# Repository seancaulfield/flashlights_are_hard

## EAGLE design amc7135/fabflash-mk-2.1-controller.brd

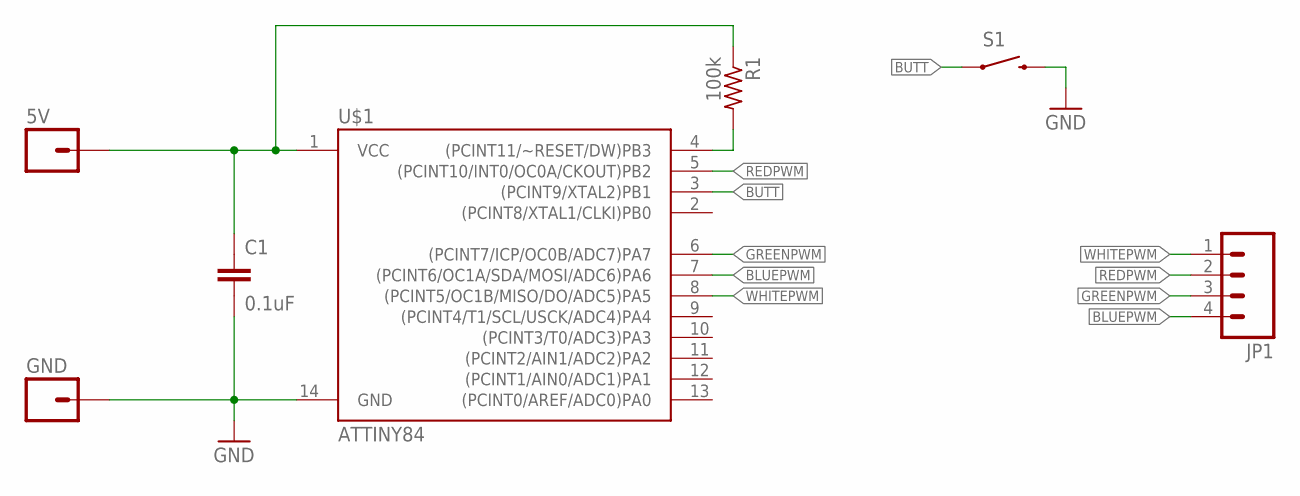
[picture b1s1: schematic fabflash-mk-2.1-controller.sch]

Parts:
5V: M01PTH-0.9MM; 1X01-0.9MM
C1: 0.1uF; C0603
GND: M01PTH-0.9MM; 1X01-0.9MM
JP1: M04JST-PTH-VERT; JST-4-PH-VERT-PTH
R1: 100k; R0603
S1: SWITCH-MOMENTARY-212MM; TACTILE-PTH-12MM
U$1: ATTINY84; SO14

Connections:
5V: 5V.1, C1.1, R1.1, U$1.1 (VCC)
BLUEPWM: JP1.4, U$1.7 ((PCINT6/OC1A/SDA/MOSI/ADC6)PA6)
BUTT: S1.1, U$1.3 ((PCINT9/XTAL2)PB1)
GND: C1.2, GND.1, S1.3 (2), U$1.14 (GND)
GREENPWM: JP1.3, U$1.6 ((PCINT7/ICP/OC0B/ADC7)PA7)
unnamed: R1.2, U$1.4 ((PCINT11/~RESET/DW)PB3)
REDPWM: JP1.2, U$1.5 ((PCINT10/INT0/OC0A/CKOUT)PB2)
WHITEPWM: JP1.1, U$1.8 ((PCINT5/OC1B/MISO/DO/ADC5)PA5)

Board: 2 copper layers, 7 parts (1 on the bottom side), 8 nets, no tracks yet.

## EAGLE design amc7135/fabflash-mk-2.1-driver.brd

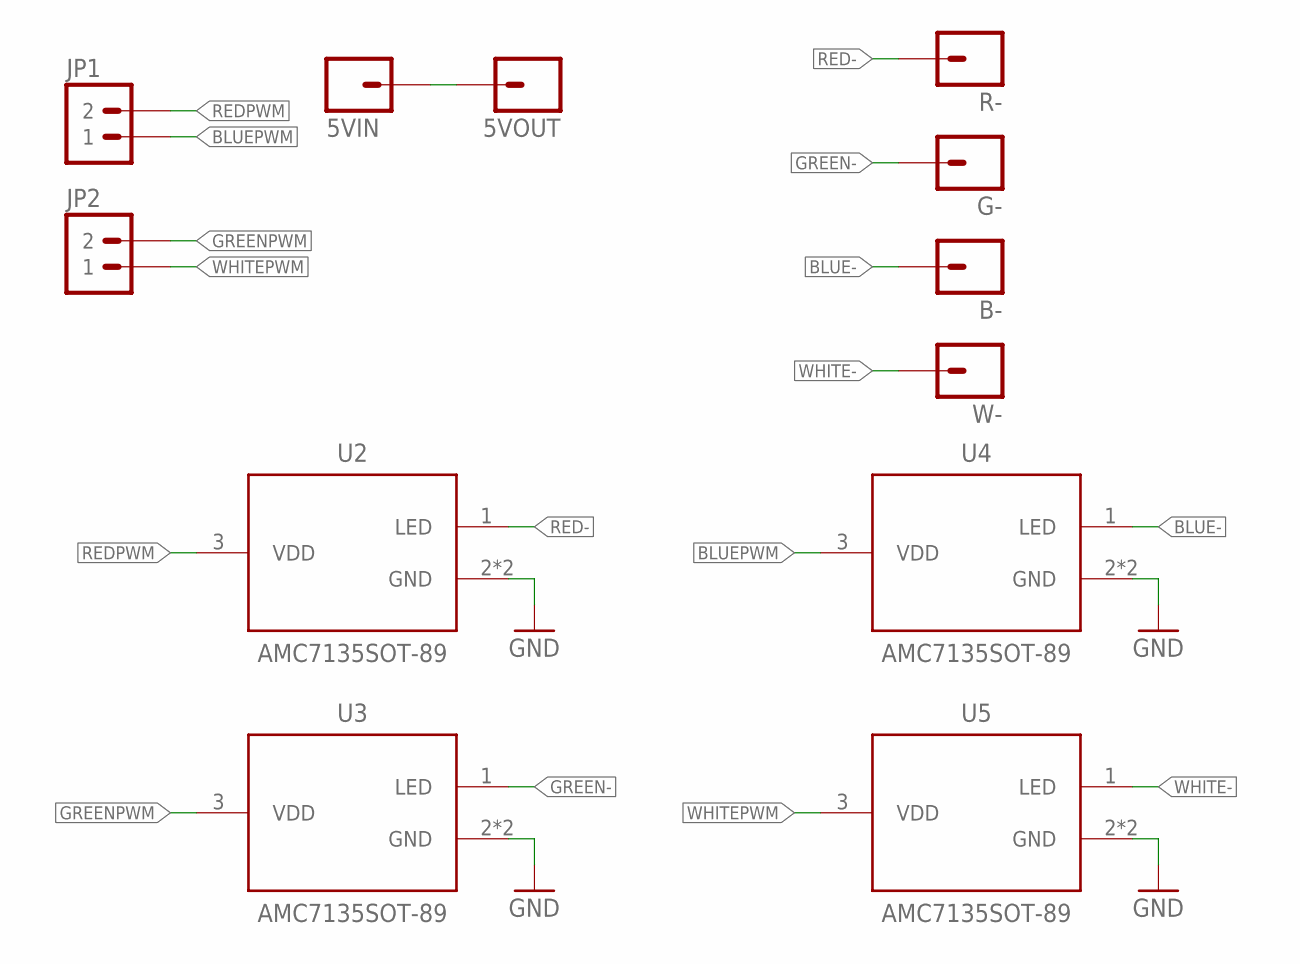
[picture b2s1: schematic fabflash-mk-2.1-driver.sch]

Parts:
5VIN, 5VOUT: M01SMD_2X3MM; 1X01_SMD_2X3MM
B-: M01SMD_2X3MM; 1X01_SMD_2X3MM
G-: M01SMD_2X3MM; 1X01_SMD_2X3MM
JP1, JP2: M02PTH-2MM; 1X02-2MM-PTH
R-: M01SMD_2X3MM; 1X01_SMD_2X3MM
U2, U3, U4, U5: AMC7135SOT-89; SOT89
W-: M01SMD_2X3MM; 1X01_SMD_2X3MM

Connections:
BLUE-: B-.P$1, U4.1 (LED)
BLUEPWM: JP1.P$1 (1), U4.3 (VDD)
GND: U2.2 (GND), U2.4 (GND), U3.2 (GND), U3.4 (GND), U4.2 (GND), U4.4 (GND), U5.2 (GND), U5.4 (GND)
GREEN-: G-.P$1, U3.1 (LED)
GREENPWM: JP2.P$2 (2), U3.3 (VDD)
unnamed: 5VIN.P$1, 5VOUT.P$1
RED-: R-.P$1, U2.1 (LED)
REDPWM: JP1.P$2 (2), U2.3 (VDD)
WHITE-: U5.1 (LED), W-.P$1
WHITEPWM: JP2.P$1 (1), U5.3 (VDD)

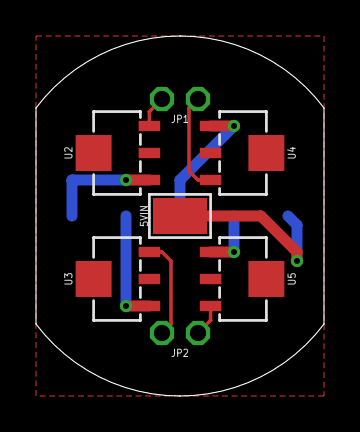
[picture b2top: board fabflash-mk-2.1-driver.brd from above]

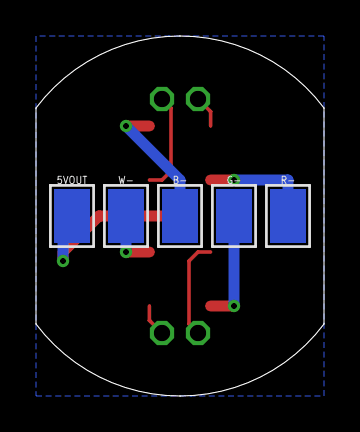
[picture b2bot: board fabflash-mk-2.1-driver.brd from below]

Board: 2 copper layers, 16.0 x 20.0 mm, 12 parts (5 on the bottom side), 10 nets.

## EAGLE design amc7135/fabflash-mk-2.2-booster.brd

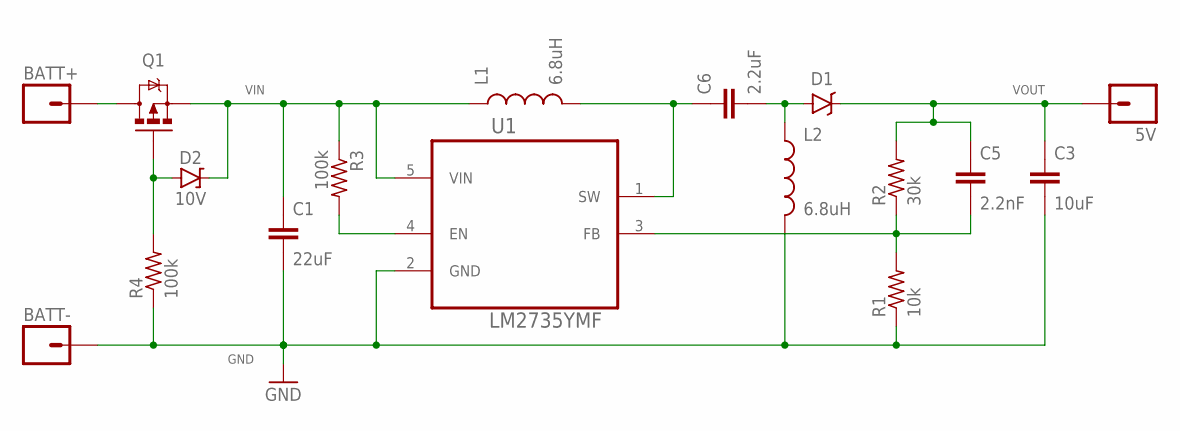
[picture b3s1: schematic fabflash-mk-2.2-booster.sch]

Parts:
5V: M01PTH-1.2MM; 1X01-1.2MM
BATT+: M01NOT-A-VIA-NOPE; 1X01_NOSILK_NOSTOP
BATT-: M01NOT-A-VIA-NOPE; 1X01_NOSILK_NOSTOP
C1: 22uF; C0805
C3: 10uF; C0805
C5: 2.2nF; C0603
C6: 2.2uF; C0805
D1: B340A; SMA-DIODE
D2: 10V; SOD123
L1, L2: 6.8uH; TAIYO-YUDEN-40XX
Q1: MOSFET-PCHANNELIRLML2244; SOT23-3
R1: 10k; R0603
R2: 30k; R0603
R3, R4: 100k; R0603
U1: LM2735YMF; SOT95P285X110-5N

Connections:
BATT+: BATT+.P$1, Q1.3 (D)
GND: BATT-.P$1, C1.2, C3.2, L2.2, R1.1, R4.1, U1.2 (GND)
unnamed: C6.1, L1.2, U1.1 (SW)
unnamed: R3.2, U1.4 (EN)
unnamed: D2.A, Q1.1 (G), R4.2
unnamed: C6.2, D1.A, L2.1
unnamed: C5.2, R1.2, R2.1, U1.3 (FB)
VIN: C1.1, D2.C, L1.1, Q1.2 (S), R3.1, U1.5 (VIN)
VOUT: 5V.P$1, C3.1, C5.1, D1.C, R2.2

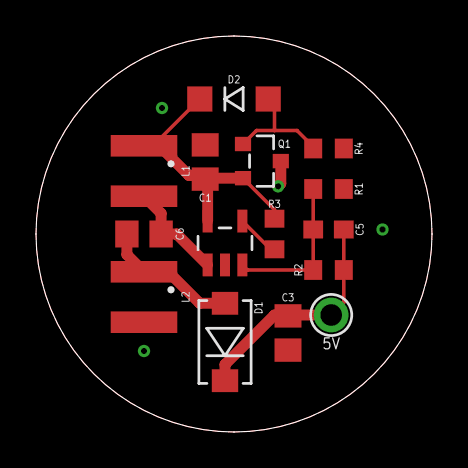
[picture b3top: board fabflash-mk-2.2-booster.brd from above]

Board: 2 copper layers, 22.0 x 22.0 mm, 17 parts (0 on the bottom side), 9 nets.

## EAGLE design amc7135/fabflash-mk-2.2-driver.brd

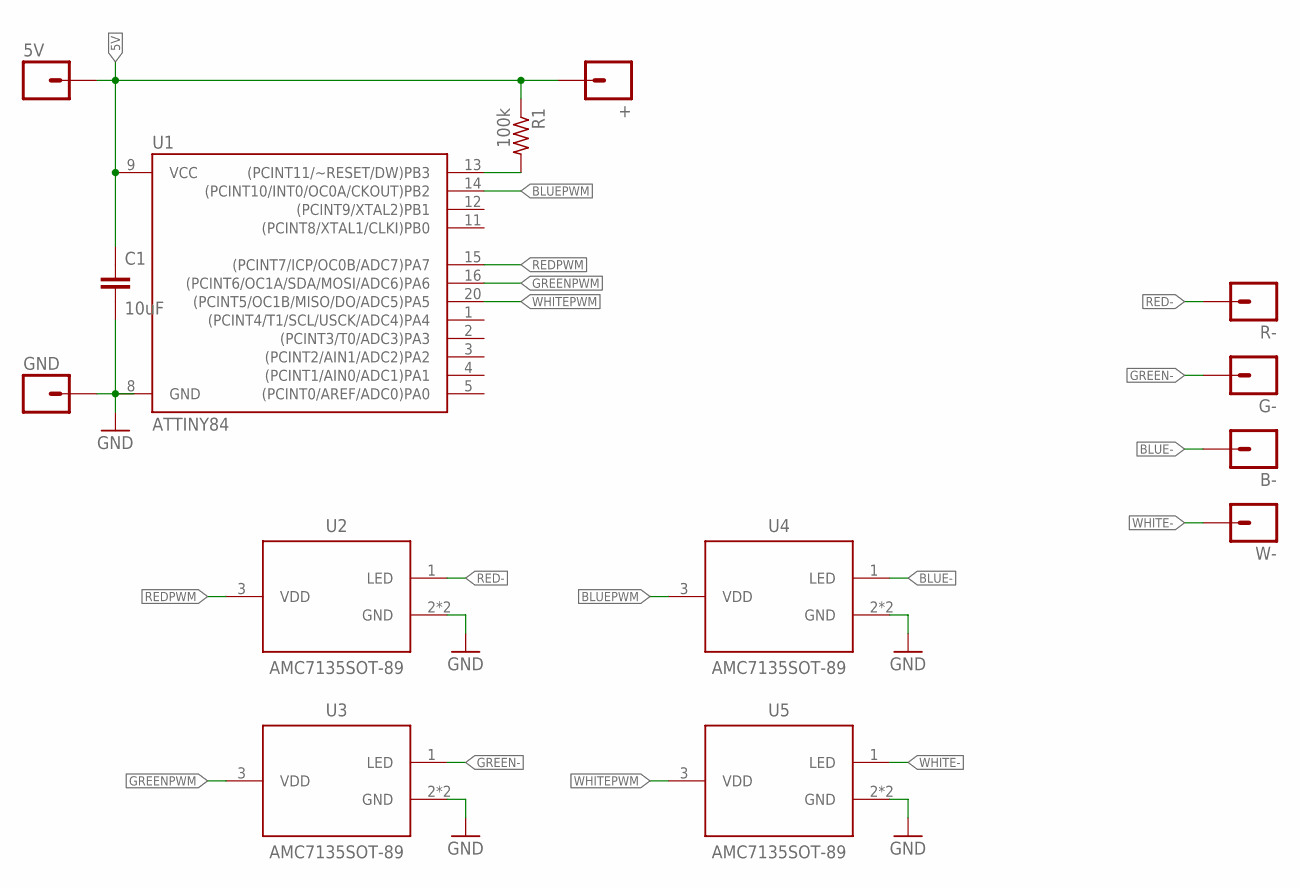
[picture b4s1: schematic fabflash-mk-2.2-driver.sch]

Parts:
5V: M01SMD_2X3MM; 1X01_SMD_2X3MM
+: M01SMD_2X3MM; 1X01_SMD_2X3MM
B-: M01SMD_2X3MM; 1X01_SMD_2X3MM
C1: 10uF; C0805
G-: M01SMD_2X3MM; 1X01_SMD_2X3MM
GND: M01NOT-A-VIA-NOPE; 1X01_NOSILK_NOSTOP
R1: 100k; R0603
R-: M01SMD_2X3MM; 1X01_SMD_2X3MM
U1: ATTINY84; QFN20
U2, U3, U4, U5: AMC7135SOT-89; SOT89
W-: M01SMD_2X3MM; 1X01_SMD_2X3MM

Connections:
5V: 5V.P$1, +.P$1, C1.1, R1.1, U1.9 (VCC)
BLUE-: B-.P$1, U4.1 (LED)
BLUEPWM: U1.14 ((PCINT10/INT0/OC0A/CKOUT)PB2), U4.3 (VDD)
GND: C1.2, GND.P$1, U1.8 (GND), U2.2 (GND), U2.4 (GND), U3.2 (GND), U3.4 (GND), U4.2 (GND), U4.4 (GND), U5.2 (GND), U5.4 (GND)
GREEN-: G-.P$1, U3.1 (LED)
GREENPWM: U1.16 ((PCINT6/OC1A/SDA/MOSI/ADC6)PA6), U3.3 (VDD)
unnamed: R1.2, U1.13 ((PCINT11/~RESET/DW)PB3)
RED-: R-.P$1, U2.1 (LED)
REDPWM: U1.15 ((PCINT7/ICP/OC0B/ADC7)PA7), U2.3 (VDD)
WHITE-: U5.1 (LED), W-.P$1
WHITEPWM: U1.20 ((PCINT5/OC1B/MISO/DO/ADC5)PA5), U5.3 (VDD)

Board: 2 copper layers, 14 parts (5 on the bottom side), 11 nets, no tracks yet.

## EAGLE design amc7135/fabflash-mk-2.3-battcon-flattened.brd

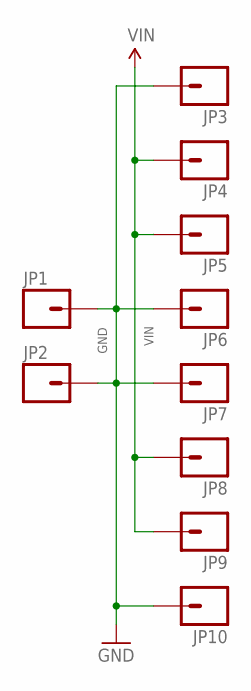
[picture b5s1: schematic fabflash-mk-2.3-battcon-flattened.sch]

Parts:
JP1, JP2: M01NOT-A-VIA-NOPE; 1X01_NOSILK_NOSTOP
JP3, JP6, JP7, JP10: M01SMD-1X2.5MM-NS; 1X01-SMD-1X2.5MM-NS
JP4, JP5, JP8, JP9: M01NOSILK-KIT; 1X01NS-KIT

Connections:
GND: JP1.P$1, JP2.P$1, JP3.1, JP6.1, JP7.1, JP10.1
VIN: JP4.1, JP5.1, JP8.1, JP9.1

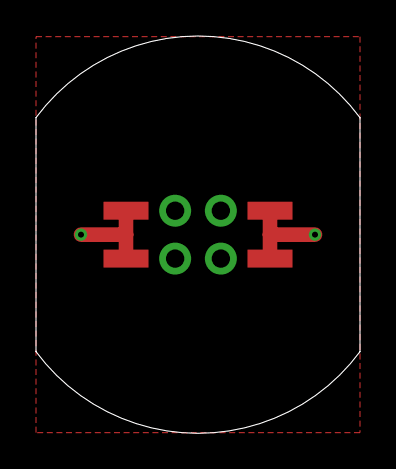
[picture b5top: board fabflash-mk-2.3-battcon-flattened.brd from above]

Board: 2 copper layers, 18.0 x 22.1 mm, 10 parts (0 on the bottom side), 2 nets.

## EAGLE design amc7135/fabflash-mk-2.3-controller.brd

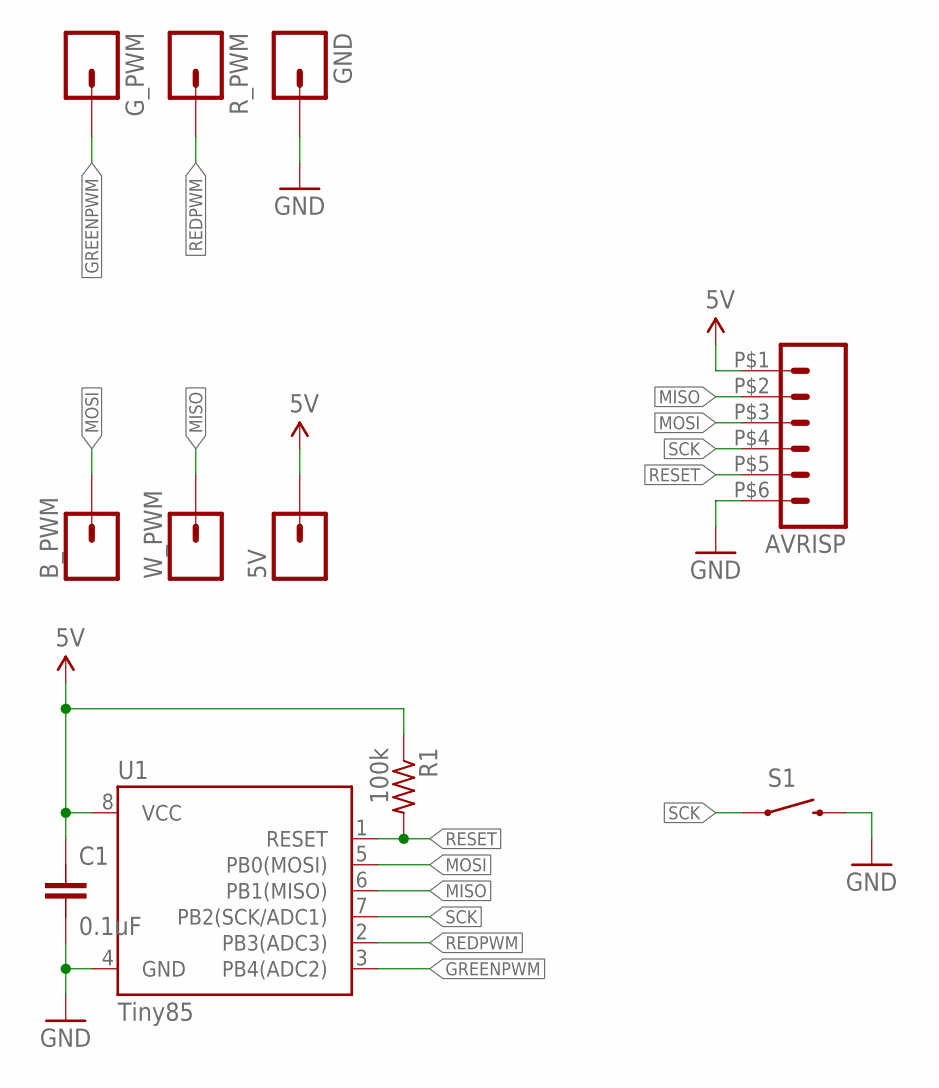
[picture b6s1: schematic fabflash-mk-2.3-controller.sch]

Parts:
5V: M01PTH-0.9MM; 1X01-0.9MM
AVRISP: M06PTH-2MM-NS; 1X06-PTH-2MM-NS
B_PWM: M01PTH-0.9MM; 1X01-0.9MM
C1: 0.1uF; C0603
GND: M01PTH-0.9MM; 1X01-0.9MM
G_PWM: M01PTH-0.9MM; 1X01-0.9MM
R1: 100k; R0603
R_PWM: M01PTH-0.9MM; 1X01-0.9MM
S1: SWITCH-MOMENTARY-2PTH; TACTILE-PTH
U1: Tiny85; SO08-EIAJ
W_PWM: M01PTH-0.9MM; 1X01-0.9MM

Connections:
5V: 5V.1, AVRISP.P$1 (1), C1.1, R1.1, U1.8 (VCC)
GND: AVRISP.P$6 (6), C1.2, GND.1, S1.3 (2), S1.4 (2), U1.4 (GND)
GREENPWM: G_PWM.1, U1.3 (PB4(ADC2))
MISO: AVRISP.P$2 (2), U1.6 (PB1(MISO)), W_PWM.1
MOSI: AVRISP.P$3 (3), B_PWM.1, U1.5 (PB0(MOSI))
REDPWM: R_PWM.1, U1.2 (PB3(ADC3))
RESET: AVRISP.P$5 (5), R1.2, U1.1 (RESET)
SCK: AVRISP.P$4 (4), S1.1, S1.2 (1), U1.7 (PB2(SCK/ADC1))

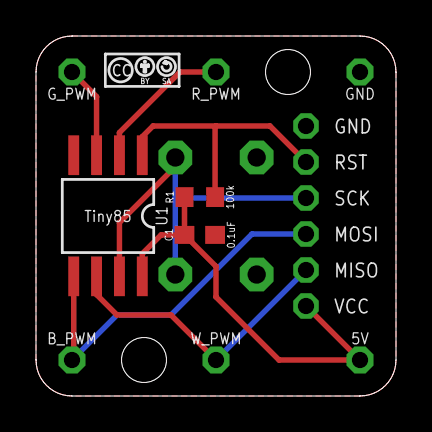
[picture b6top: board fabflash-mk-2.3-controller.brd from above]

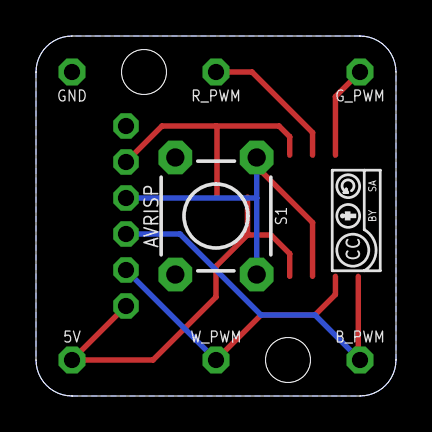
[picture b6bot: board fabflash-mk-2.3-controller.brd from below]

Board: 2 copper layers, 20.0 x 20.0 mm, 13 parts (3 on the bottom side), 8 nets.

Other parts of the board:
U$1: CC-BY-SA-4.0-NO-URL
U$2: CC-BY-SA-4.0-SMALL
